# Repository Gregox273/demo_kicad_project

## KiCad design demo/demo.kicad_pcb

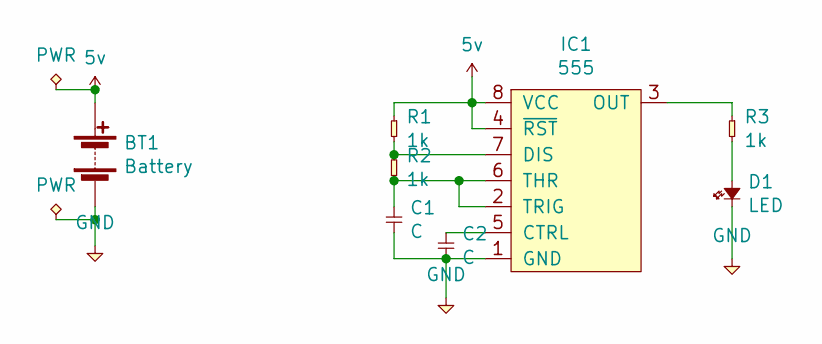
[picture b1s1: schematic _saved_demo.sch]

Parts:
BT1: Battery; SIL-254P-02
C1, C2: C; 0603
D1: LED; 0603-LED
IC1: 555; SOIC-8; Farnell 9589880
R1, R2, R3: 1k; 0603

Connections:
5v: BT1.1 (+), IC1.4 (~RST), IC1.8 (VCC), R1.1
GND: BT1.2 (-), C1.1, C2.1, D1.1, IC1.1 (GND)
unnamed: C1.2, IC1.2 (TRIG), IC1.6 (THR), R2.1
unnamed: C2.2, IC1.5 (CTRL)
unnamed: D1.2, R3.2
unnamed: IC1.3 (OUT), R3.1
unnamed: IC1.7 (DIS), R1.2, R2.2

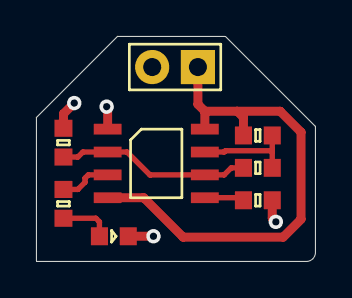
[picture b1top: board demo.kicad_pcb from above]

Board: 2 copper layers, 15.5 x 12.5 mm, 8 parts (0 on the bottom side), 7 nets.
